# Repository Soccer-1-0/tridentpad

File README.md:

# Tridentpad

The Tridentpad has 12 keys, with each key having a backlight SK6812 MINI-E LEDs, and uses QMK software.

Demo link: https://youtu.be/PokkB0xyun4 

## Zine Poster

## CAD

I loved designing this macropad, and this is my first hardware project from HackClub! This project is mainly for personal use (I haven't really decided yet), and also just as a fun learning project to get started in making hardware projects.

## Schematic 

## PCB

## Firmware

This hackpad uses QMK Firmware to set up the keys and keymap. I will use Vial later to reset the keys, but for now, the keys are simply the left 3x4 letters on a keyboard.

## Case

The case is connected with 4x M3x16mm Screws and 4x M3x5mx4mm heatset insert. The case is printed in two parts and held together with the screws and inserts.

## Assembly

Assembly

https://github.com/user-attachments/assets/bcddb715-b996-4dae-9dc9-fb0daacc86bf

Unassembly

https://github.com/user-attachments/assets/65befd96-f695-466a-b2bf-0598ded5cfb7

## BOM

Everything you need to make this hackpad!
The BOM are in the files.

### Components

- PCB x1
- Seeed XIAO RP2040 x1
- MX-Style switches x12
- 1N4148 Diodes x12
- DSA keycaps x12
- SK6812 MINI-E LED x12
- M3x16mm screw x4
- M3x5mx4mm heatset insert x4
- Case, two parts

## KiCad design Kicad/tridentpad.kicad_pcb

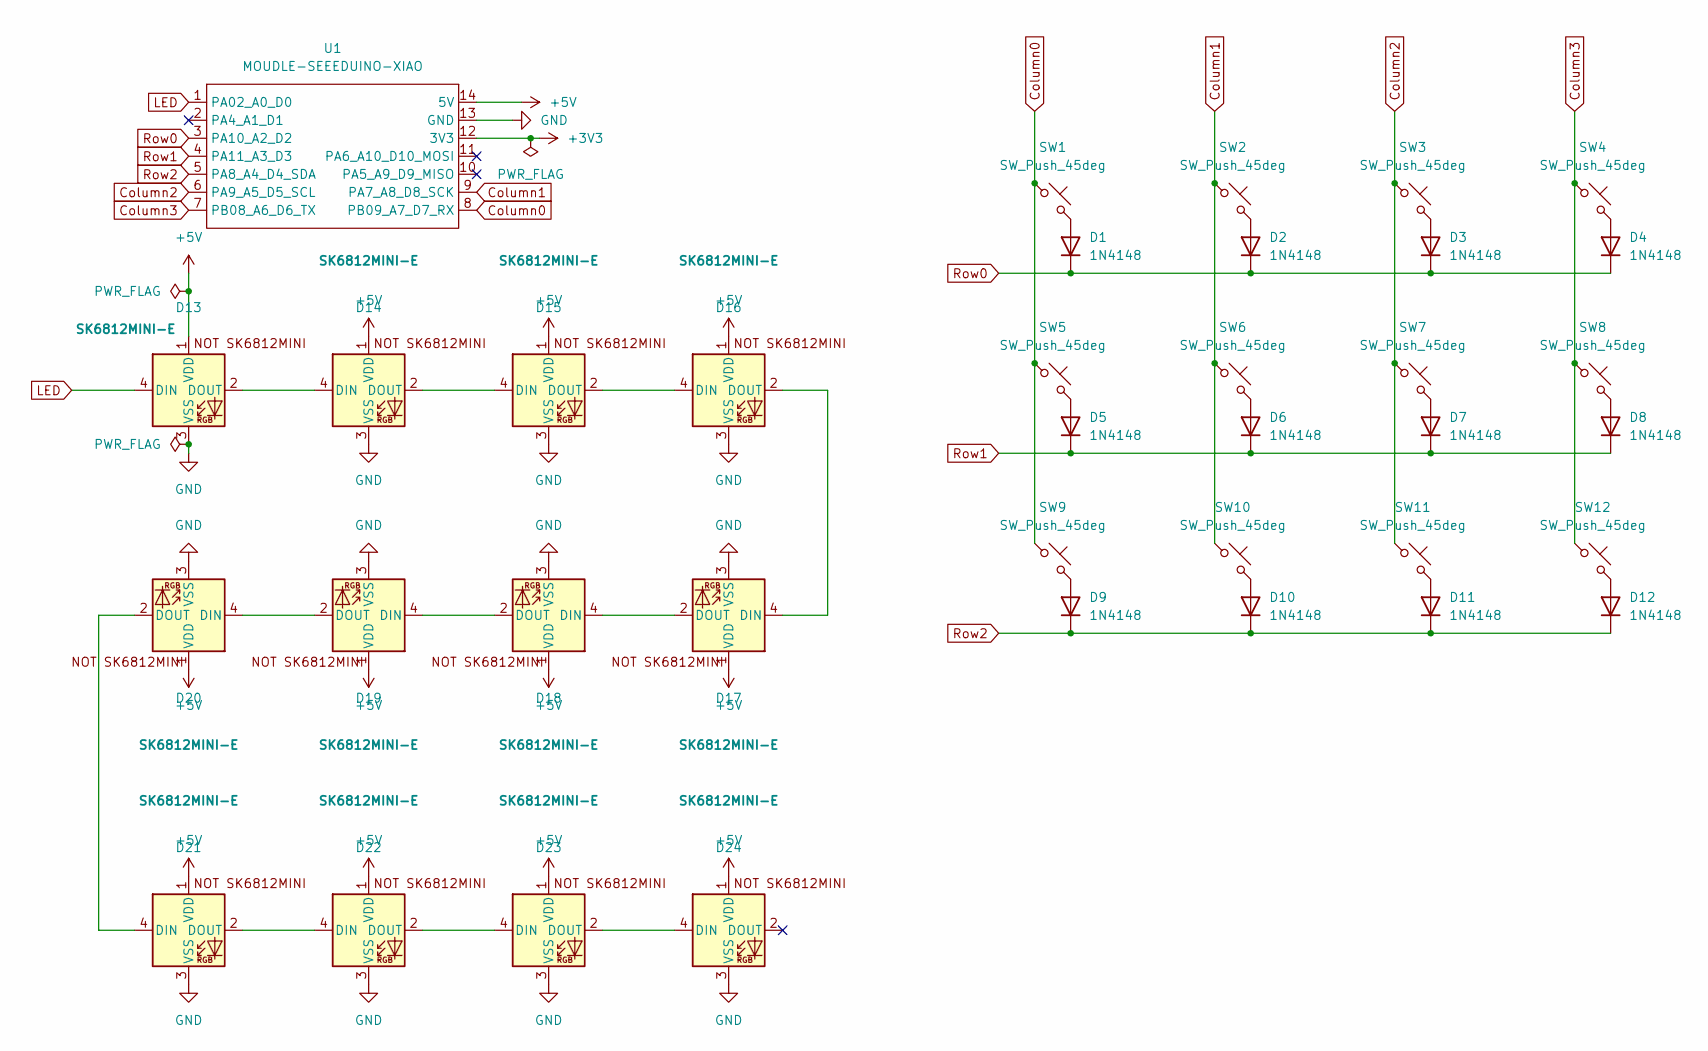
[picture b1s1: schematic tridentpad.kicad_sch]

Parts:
D1, D2, D3, D4, D5, D6, D7, D8, D9, D10, D11, D12: 1N4148; D_DO-35_SOD27_P7.62mm_Horizontal
D13, D14, D15, D16, D17, D18, D19, D20, D21, D22, D23, D24: SK6812MINI-E; SK6812MINI-E_fixed
SW1, SW2, SW3, SW4, SW5, SW6, SW7, SW8, SW9, SW10, SW11, SW12: SW_Push_45deg; SW_Cherry_MX_1.00u_PCB
U1: MOUDLE-SEEEDUINO-XIAO; XIAO-Generic-Hybrid-14P-2.54-21X17.8MM

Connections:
+3V3: U1.12 (3V3)
+5V: D13.1 (VDD), D14.1 (VDD), D15.1 (VDD), D16.1 (VDD), D17.1 (VDD), D18.1 (VDD), D19.1 (VDD), D20.1 (VDD), D21.1 (VDD), D22.1 (VDD), D23.1 (VDD), D24.1 (VDD), U1.14 (5V)
Column0: SW1.1, SW5.1, SW9.1, U1.8 (PB09_A7_D7_RX)
Column1: SW2.1, SW6.1, SW10.1, U1.9 (PA7_A8_D8_SCK)
Column2: SW3.1, SW7.1, SW11.1, U1.6 (PA9_A5_D5_SCL)
Column3: SW4.1, SW8.1, SW12.1, U1.7 (PB08_A6_D6_TX)
GND: D13.3 (VSS), D14.3 (VSS), D15.3 (VSS), D16.3 (VSS), D17.3 (VSS), D18.3 (VSS), D19.3 (VSS), D20.3 (VSS), D21.3 (VSS), D22.3 (VSS), D23.3 (VSS), D24.3 (VSS), U1.13 (GND)
LED: D13.4 (DIN), U1.1 (PA02_A0_D0)
unnamed: D1.2 (A), SW1.2
unnamed: D2.2 (A), SW2.2
unnamed: D3.2 (A), SW3.2
unnamed: D4.2 (A), SW4.2
unnamed: D5.2 (A), SW5.2
unnamed: D6.2 (A), SW6.2
unnamed: D7.2 (A), SW7.2
unnamed: D8.2 (A), SW8.2
unnamed: D9.2 (A), SW9.2
unnamed: D10.2 (A), SW10.2
unnamed: D11.2 (A), SW11.2
unnamed: D12.2 (A), SW12.2
unnamed: D13.2 (DOUT), D14.4 (DIN)
unnamed: D14.2 (DOUT), D15.4 (DIN)
unnamed: D15.2 (DOUT), D16.4 (DIN)
unnamed: D16.2 (DOUT), D17.4 (DIN)
unnamed: D17.2 (DOUT), D18.4 (DIN)
unnamed: D18.2 (DOUT), D19.4 (DIN)
unnamed: D19.2 (DOUT), D20.4 (DIN)
unnamed: D20.2 (DOUT), D21.4 (DIN)
unnamed: D21.2 (DOUT), D22.4 (DIN)
unnamed: D22.2 (DOUT), D23.4 (DIN)
unnamed: D23.2 (DOUT), D24.4 (DIN)
Row0: D1.1 (K), D2.1 (K), D3.1 (K), D4.1 (K), U1.3 (PA10_A2_D2)
Row1: D5.1 (K), D6.1 (K), D7.1 (K), D8.1 (K), U1.4 (PA11_A3_D3)
Row2: D9.1 (K), D10.1 (K), D11.1 (K), D12.1 (K), U1.5 (PA8_A4_D4_SDA)

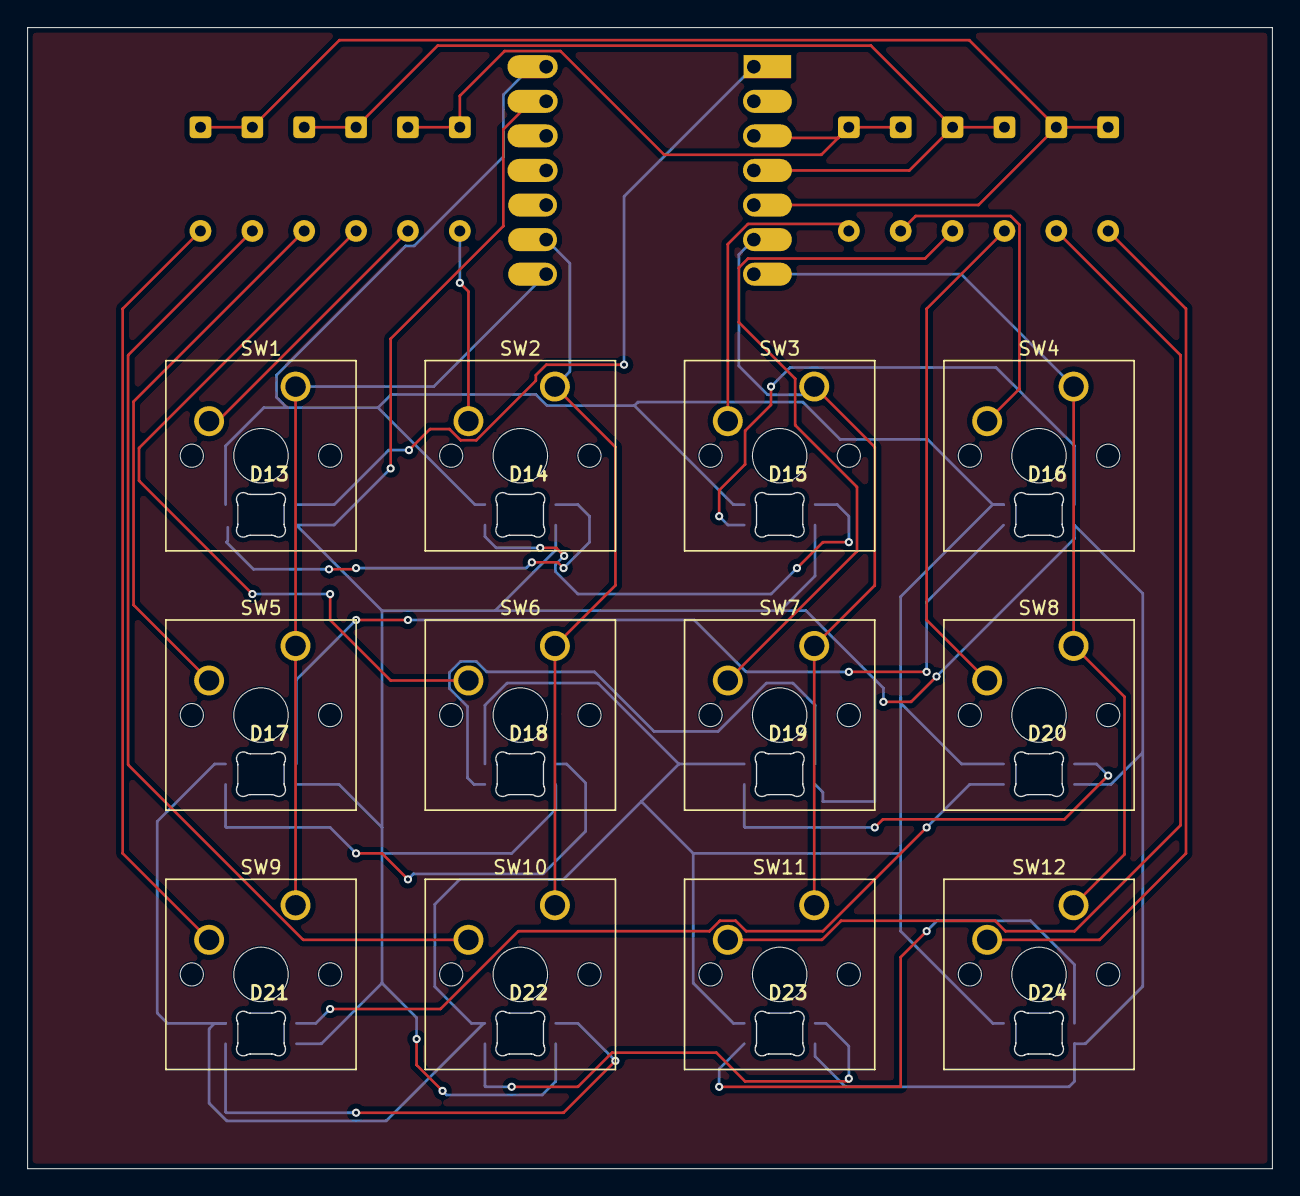
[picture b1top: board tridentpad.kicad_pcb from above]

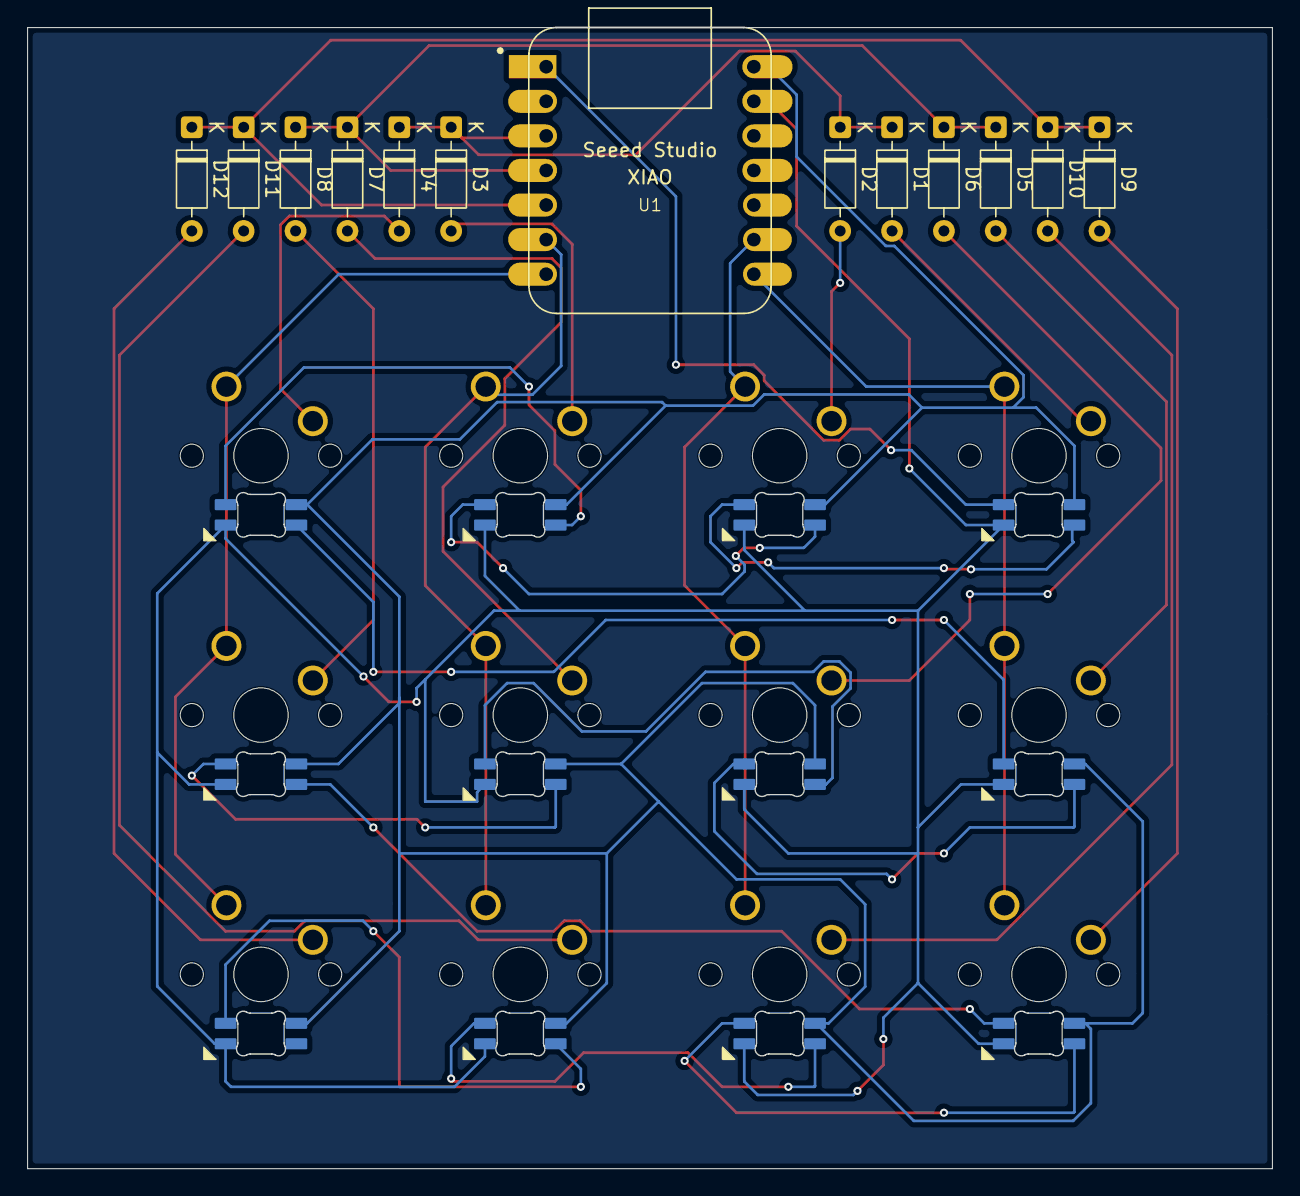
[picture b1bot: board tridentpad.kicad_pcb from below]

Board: 2 copper layers, 91.4 x 83.8 mm, 37 parts (13 on the bottom side), 33 nets.

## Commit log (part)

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2026-05-30 Rename Casing Bottom.png to CasingBottom.png
2026-05-30 Rename Casing Top.png to CasingTop.png
2026-05-30 Rename assembly v10.mp4 to assembly.mp4
